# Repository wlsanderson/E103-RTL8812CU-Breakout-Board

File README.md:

# E103-RTL8812CU-Breakout-Board
Breakout board for the Ebyte E103-RTL8812CU module.

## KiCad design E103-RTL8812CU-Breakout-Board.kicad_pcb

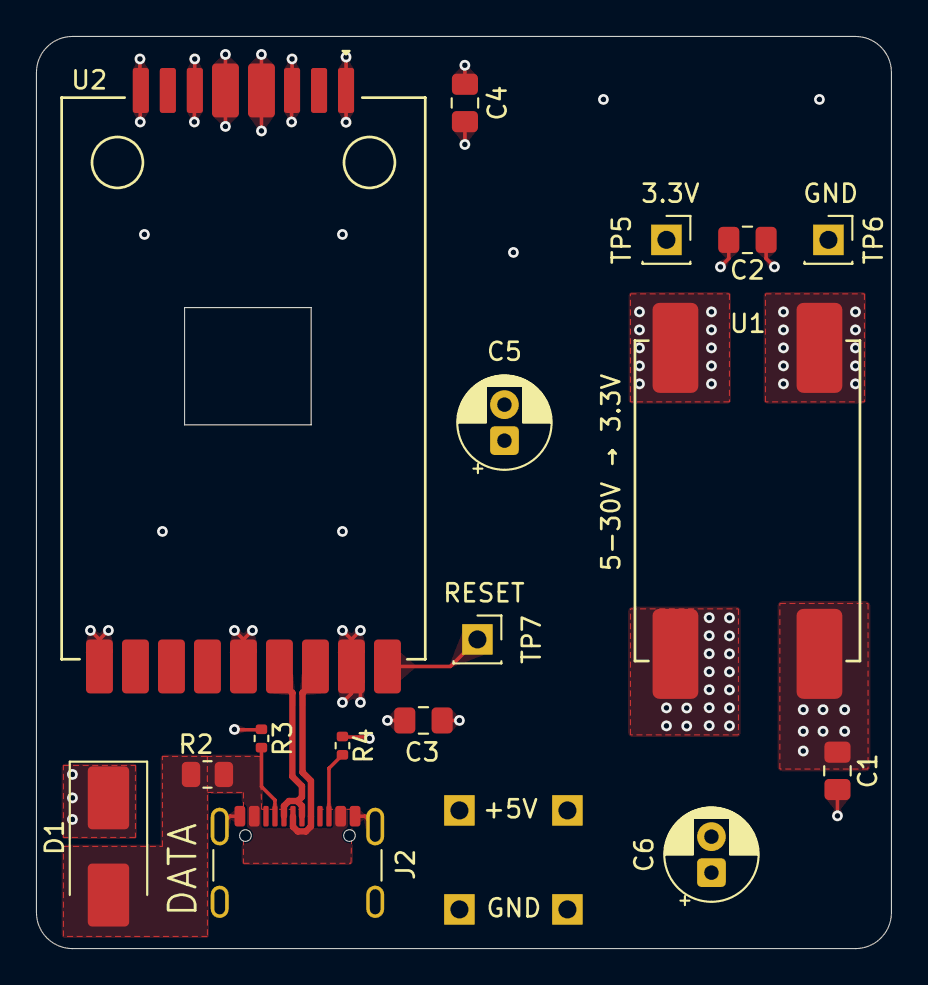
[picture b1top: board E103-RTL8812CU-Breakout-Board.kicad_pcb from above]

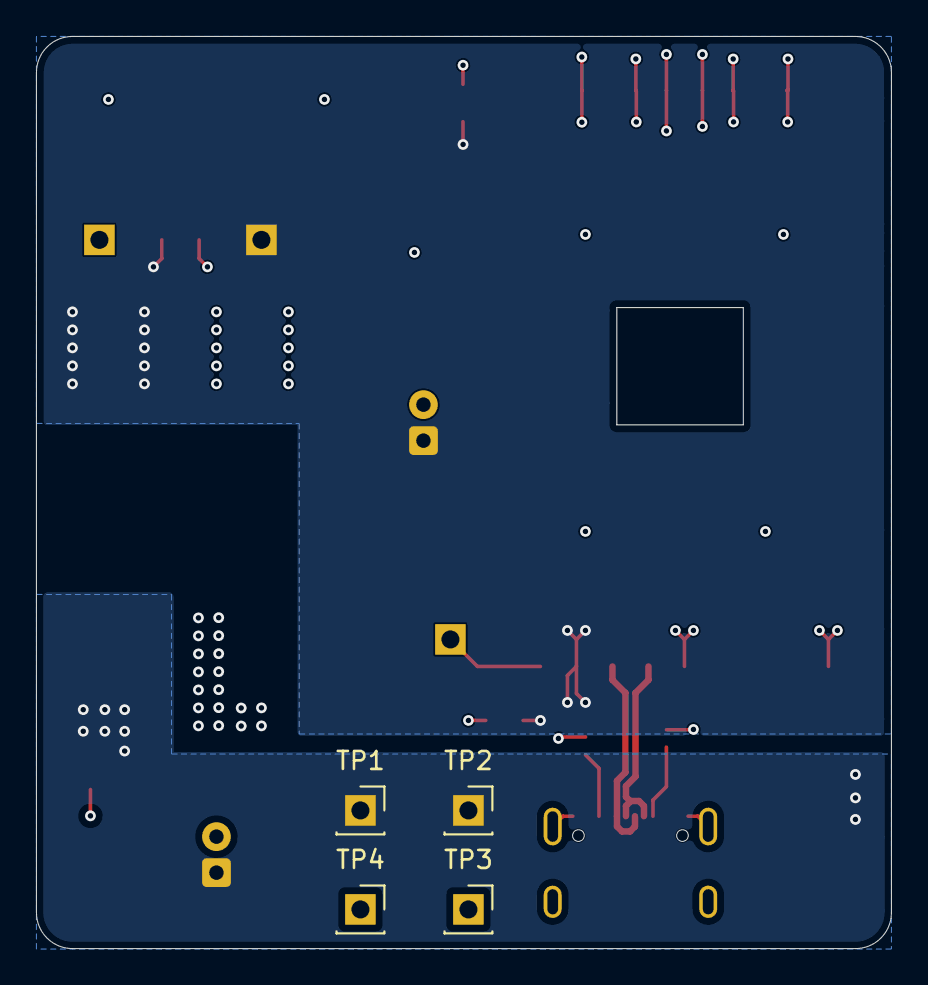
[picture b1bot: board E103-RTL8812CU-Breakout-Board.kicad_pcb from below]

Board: 4 copper layers, 47.5 x 50.7 mm, 20 parts (4 on the bottom side), 10 nets.

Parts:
C1, C2: 10u; C_0805_2012Metric_Pad1.18x1.45mm_HandSolder
C3, C4: 1u; C_0805_2012Metric_Pad1.18x1.45mm_HandSolder
C5, C6: 47u; CP_Radial_D5.0mm_P2.00mm
D1: VS-10BQ015-M3; D_SMB_Handsoldering
J2: USB_C_Receptacle_USB2.0_16P; USB_C_Receptacle_GCT_USB4105-xx-A_16P_TopMnt_Horizontal
R2: 0; R_0805_2012Metric
R3, R4: 5.1k; R_0402_1005Metric
TP1, TP2, TP3, TP4: Clip On; PinSocket_1x01_P2.54mm_Vertical
TP5, TP6, TP7: Pin; PinSocket_1x01_P2.54mm_Vertical
U1: Buck_Converter_3.3V; AKEYSRC 3.3V Buck Converter
U2: E103-RTL8812CU

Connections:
+3.3V: C2.1, C3.1, C4.1, C5.1, TP5.1 (1_1), U1.2 (OUT), U2.16 (VDD)
/CC1: J2.A5 (CC1), R3.2
/CC2: J2.B5 (CC2), R4.2
/USB +: J2.A6 (D+), J2.B6 (D+), U2.15 (DP)
/USB -: J2.A7 (D-), J2.B7 (D-), U2.14 (DM)
/V_IN: C1.1, C6.1, D1.1 (K), TP1.1 (1_1), TP2.1 (1_1), U1.1 (IN)
GND: C1.2, C2.2, C3.2, C4.2, C5.2, C6.2, J2.A1 (GND), J2.A12 (GND), J2.B1 (GND), J2.B12 (GND), J2.SH (SHIELD), R3.1, R4.1, TP3.1 (1_1), TP4.1 (1_1), TP6.1 (1_1), U1.3 (GND), U1.4 (GND), U2.1 (GND), U2.3 (GND), U2.4 (GND), U2.5 (GND), U2.6 (GND), U2.8 (GND), U2.9 (GND), U2.13 (GND)
unnamed: D1.2 (A), R2.1
unnamed: J2.A4 (VBUS), J2.A9 (VBUS), J2.B4 (VBUS), J2.B9 (VBUS), R2.2
unnamed: TP7.1 (1_1), U2.17 (RESET)
